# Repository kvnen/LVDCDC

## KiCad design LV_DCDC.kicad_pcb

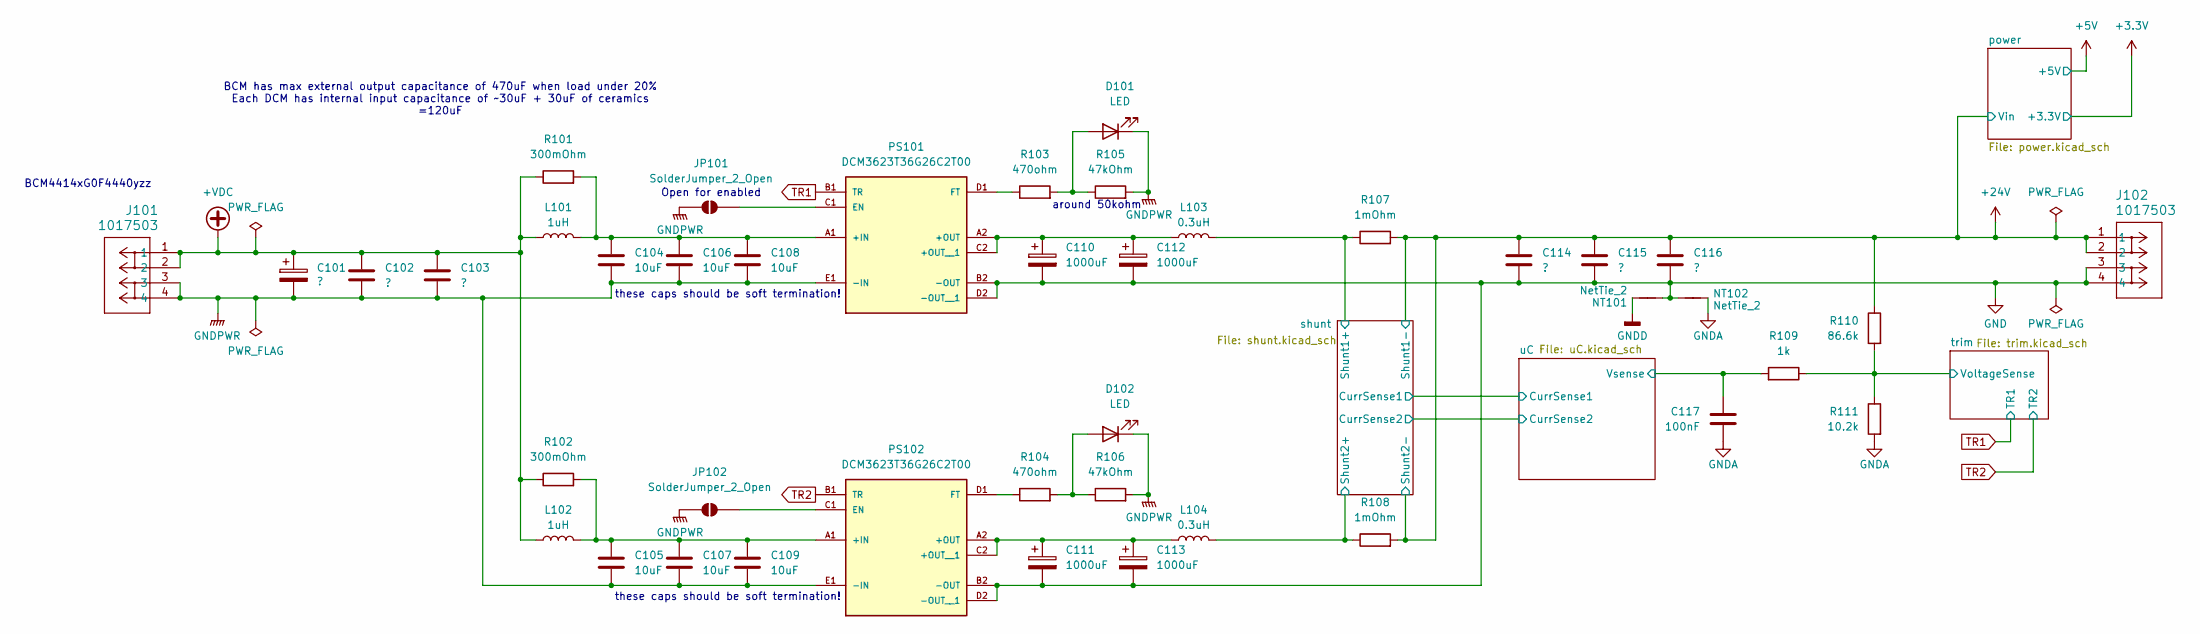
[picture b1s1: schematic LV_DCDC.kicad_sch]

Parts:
C101: ?; CP_Radial_D12.5mm_P5.00mm
C102, C103, C114, C115, C116: ?; C_1206_3216Metric
C104, C105, C106, C107, C108, C109: 10uF; C_1206_3216Metric
C110, C111, C112, C113: 1000uF; CP_Radial_D12.5mm_P5.00mm
C117: 100nF; C_0603_1608Metric
D101, D102: LED; LED_0603_1608Metric
J101, J102: 1017503; CONN_1017491
JP101, JP102: SolderJumper_2_Open; SolderJumper-2_P1.3mm_Open_TrianglePad1.0x1.5mm
L101, L102: 1uH; L_Bourns_SRP1770TA_16.9x16.9mm
L103, L104: 0.3uH; L_APV_APH1040
NT101, NT102: NetTie_2; NetTie-2_SMD_Pad2.0mm
PS101, PS102: DCM3623T36G26C2T00; CONV_DCM3623T36G26C2T00; PARTREV 1.2
R101, R102: 300mOhm; R_1206_3216Metric
R103, R104: 470ohm; R_0603_1608Metric
R105, R106: 47kOhm; R_0603_1608Metric
R107, R108: 1mOhm; R_2512_6332Metric
R109: 1k; R_0603_1608Metric
R110: 86.6k; R_0603_1608Metric
R111: 10.2k; R_0603_1608Metric

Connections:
+24V: C114.1, C115.1, C116.1, J102.1, J102.2, R107.2, R108.2, R110.1; also elsewhere on the board
+VDC: C101.1, C102.1, C103.1, J101.1, J101.2, L101.1, L102.1, R101.1, R102.1
/shunt/Shunt1+: L103.2, R107.1; also elsewhere on the board
/shunt/Shunt2+: L104.2, R108.1; also elsewhere on the board
/trim/VoltageSense: R109.1, R110.2, R111.1; also elsewhere on the board
/uC/Vsense: C117.1, R109.2; also elsewhere on the board
GND: C110.2, C111.2, C112.2, C113.2, C114.2, C115.2, C116.2, J102.3, J102.4, NT101.2, NT102.2, PS101.B2 (-OUT), PS101.D2 (-OUT__1), PS102.B2 (-OUT), PS102.D2 (-OUT__1)
GNDA: C117.2, NT102.1, R111.2; also elsewhere on the board
GNDD: NT101.1; also elsewhere on the board
GNDPWR: C101.2, C102.2, C103.2, C104.2, C105.2, C106.2, C107.2, C108.2, C109.2, D101.1 (K), D102.1 (K), J101.3, J101.4, JP101.2 (B), JP102.2 (B), PS101.E1 (-IN), PS102.E1 (-IN), R105.2, R106.2; also elsewhere on the board
unnamed: D101.2 (A), R103.2, R105.1
unnamed: D102.2 (A), R104.2, R106.1
unnamed: JP101.1 (A), PS101.C1 (EN)
unnamed: JP102.1 (A), PS102.C1 (EN)
unnamed: C104.1, C106.1, C108.1, L101.2, PS101.A1 (+IN), R101.2
unnamed: C110.1, C112.1, L103.1, PS101.A2 (+OUT), PS101.C2 (+OUT__1)
unnamed: PS101.D1 (FT), R103.1
unnamed: C105.1, C107.1, C109.1, L102.2, PS102.A1 (+IN), R102.2
unnamed: C111.1, C113.1, L104.1, PS102.A2 (+OUT), PS102.C2 (+OUT__1)
unnamed: PS102.D1 (FT), R104.1
TR1: PS101.B1 (TR); also elsewhere on the board
TR2: PS102.B1 (TR); also elsewhere on the board

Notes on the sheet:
around 50kohm
Open for enabled
these caps should be soft termination!
BCM has max external output capacitance of 470uF when load under 20% Each DCM has internal input capacitance of ~30uF + 30uF of ceramics =120uF
BCM4414xG0F4440yzz

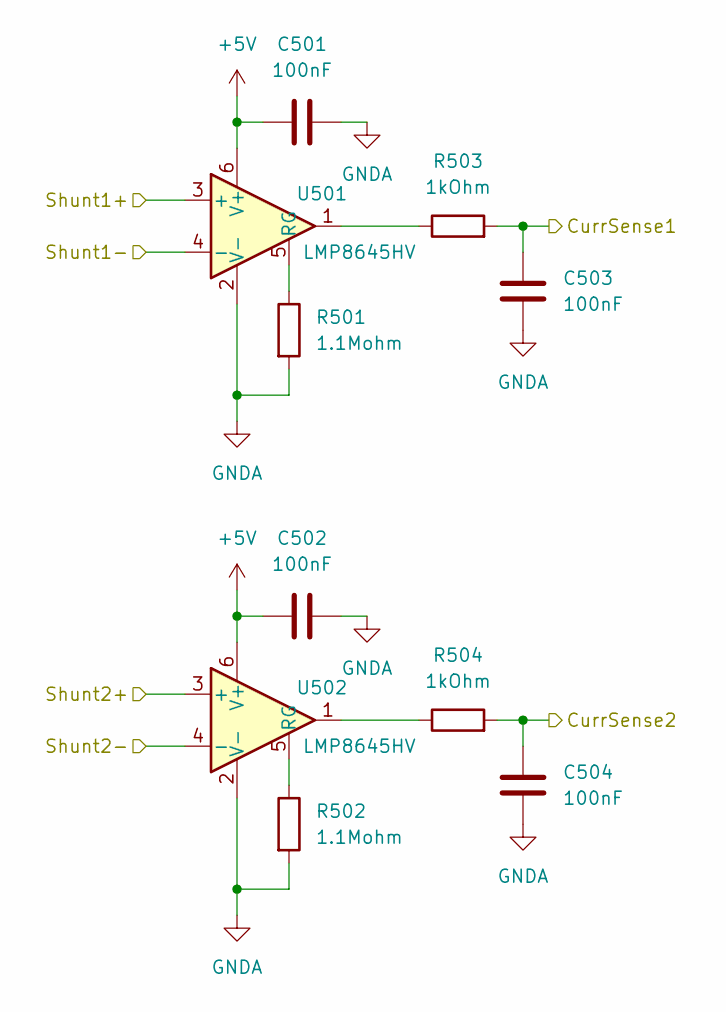
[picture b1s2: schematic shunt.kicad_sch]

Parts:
C501, C502, C503, C504: 100nF; C_0603_1608Metric
R501, R502: 1.1Mohm; R_0603_1608Metric
R503, R504: 1kOhm; R_0603_1608Metric
U501, U502: LMP8645HV; TSOT-23-6_HandSoldering

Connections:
+5V: C501.1, C502.1, U501.6 (V+), U502.6 (V+); also elsewhere on the board
+24V: U501.4 (-), U502.4 (-); also elsewhere on the board
/shunt/CurrSense1: C503.1, R503.2; also elsewhere on the board
/shunt/CurrSense2: C504.1, R504.2; also elsewhere on the board
/shunt/Shunt1+: U501.3 (+); also elsewhere on the board
/shunt/Shunt2+: U502.3 (+); also elsewhere on the board
GNDA: C501.2, C502.2, C503.2, C504.2, R501.2, R502.2, U501.2 (V-), U502.2 (V-); also elsewhere on the board
unnamed: R503.1, U501.1
unnamed: R504.1, U502.1
unnamed: R501.1, U501.5 (RG)
unnamed: R502.1, U502.5 (RG)

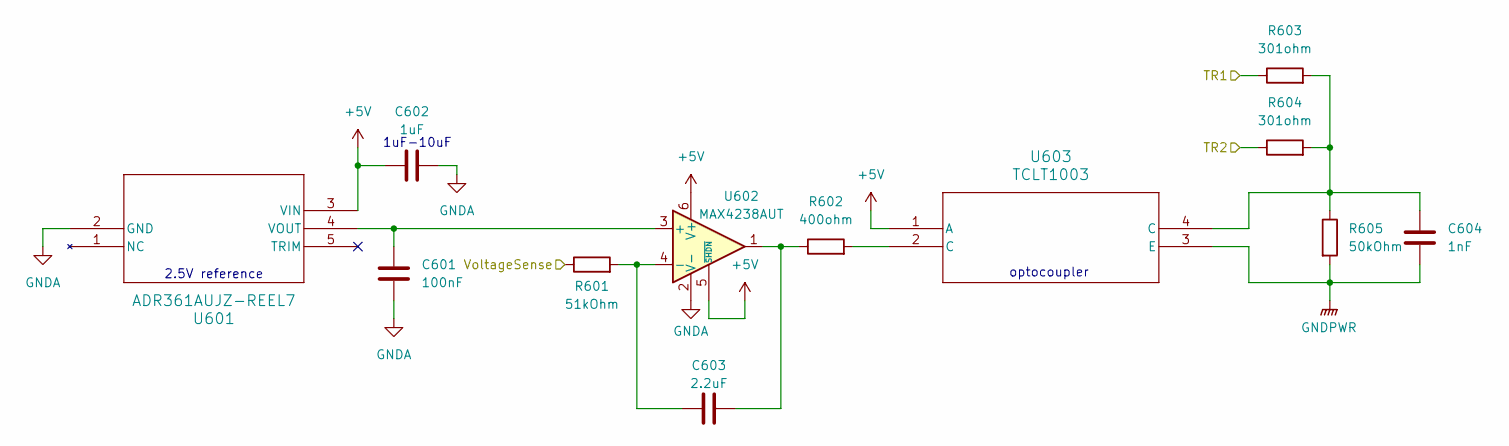
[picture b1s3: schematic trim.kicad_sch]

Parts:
C601: 100nF; C_0603_1608Metric
C602: 1uF; C_0603_1608Metric
C603: 2.2uF; C_0603_1608Metric
C604: 1nF; C_0603_1608Metric
R601: 51kOhm; R_0603_1608Metric
R602: 400ohm; R_0603_1608Metric
R603, R604: 301ohm; R_0603_1608Metric
R605: 50kOhm; R_0603_1608Metric
U601: ADR361AUJZ-REEL7; UJ_5_ADI
U602: MAX4238AUT; SOT-23-6
U603: TCLT1003; SOP-4L_TC

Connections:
+5V: C602.1, U601.3 (VIN), U602.5 (~SHDN), U602.6 (V+), U603.1 (A); also elsewhere on the board
/trim/VoltageSense: R601.1; also elsewhere on the board
GNDA: C601.2, C602.2, U601.2 (GND), U602.2 (V-); also elsewhere on the board
GNDPWR: C604.2, R605.2, U603.3 (E); also elsewhere on the board
unnamed: C603.2, R602.1, U602.1
unnamed: C604.1, R603.2, R604.2, R605.1, U603.4 (C)
unnamed: R602.2, U603.2 (C)
unnamed: C601.1, U601.4 (VOUT), U602.3 (+)
unnamed: C603.1, R601.2, U602.4 (-)
TR1: R603.1; also elsewhere on the board
TR2: R604.1; also elsewhere on the board

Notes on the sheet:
2.5V reference
optocoupler
1uF-10uF

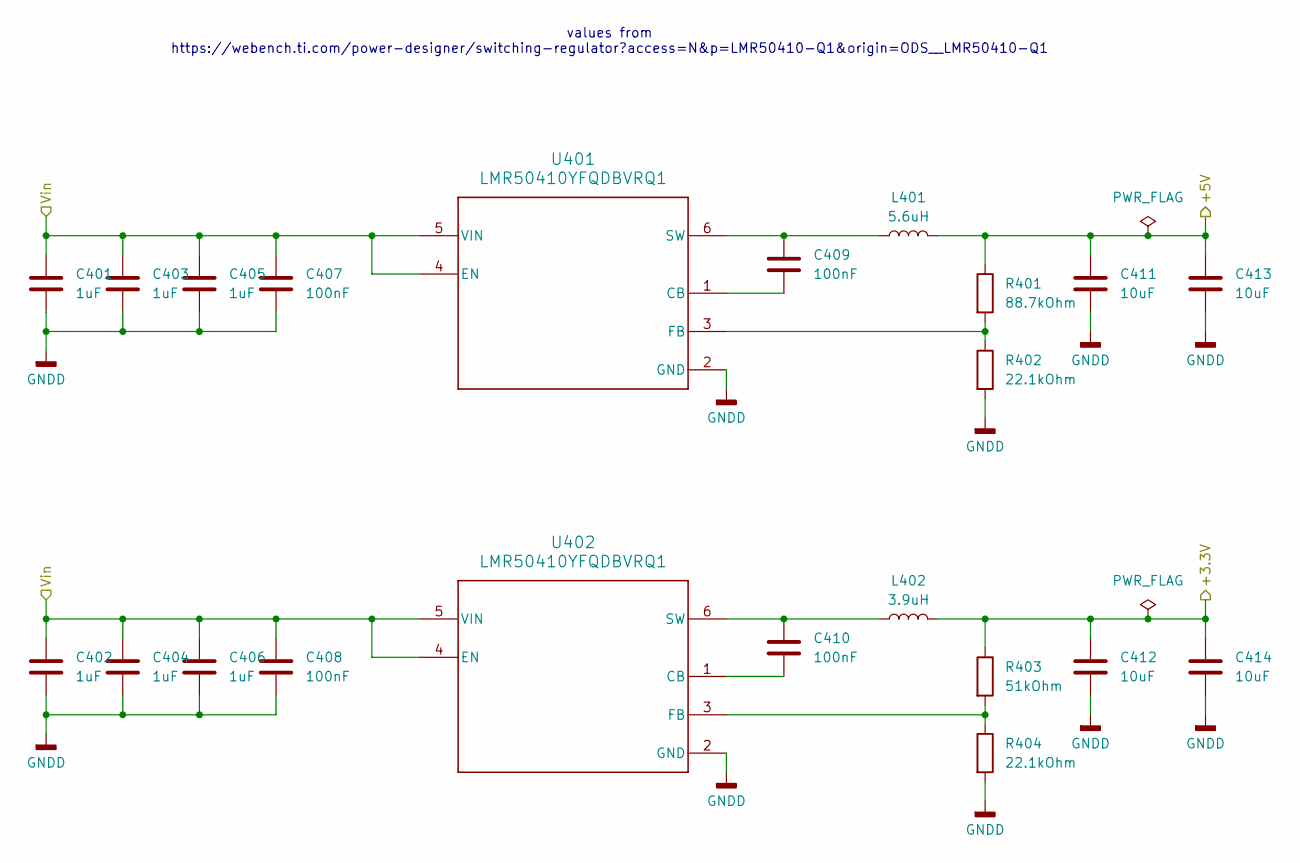
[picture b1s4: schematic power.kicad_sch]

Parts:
C401, C402, C403, C404, C405, C406: 1uF; C_1206_3216Metric
C407, C408, C409, C410: 100nF; C_0603_1608Metric
C411, C412, C413, C414: 10uF; C_1206_3216Metric
L401: 5.6uH; L_1812_4532Metric
L402: 3.9uH; L_1812_4532Metric
R401: 88.7kOhm; R_0603_1608Metric
R402, R404: 22.1kOhm; R_0603_1608Metric
R403: 51kOhm; R_0603_1608Metric
U401, U402: LMR50410YFQDBVRQ1; DBV0006A-IPC_A

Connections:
+3.3V: C412.1, C414.1, L402.2, R403.1; also elsewhere on the board
+5V: C411.1, C413.1, L401.2, R401.1; also elsewhere on the board
+24V: C401.1, C402.1, C403.1, C404.1, C405.1, C406.1, C407.1, C408.1, U401.4 (EN), U401.5 (VIN), U402.4 (EN), U402.5 (VIN); also elsewhere on the board
GNDD: C401.2, C402.2, C403.2, C404.2, C405.2, C406.2, C407.2, C408.2, C411.2, C412.2, C413.2, C414.2, R402.2, R404.2, U401.2 (GND), U402.2 (GND); also elsewhere on the board
unnamed: C409.2, U401.1 (CB)
unnamed: R401.2, R402.1, U401.3 (FB)
unnamed: C409.1, L401.1, U401.6 (SW)
unnamed: C410.2, U402.1 (CB)
unnamed: R403.2, R404.1, U402.3 (FB)
unnamed: C410.1, L402.1, U402.6 (SW)

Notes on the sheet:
values from https://webench.ti.com/power-designer/switching-regulator?access=N&p=LMR50410-Q1&origin=ODS__LMR50410-Q1

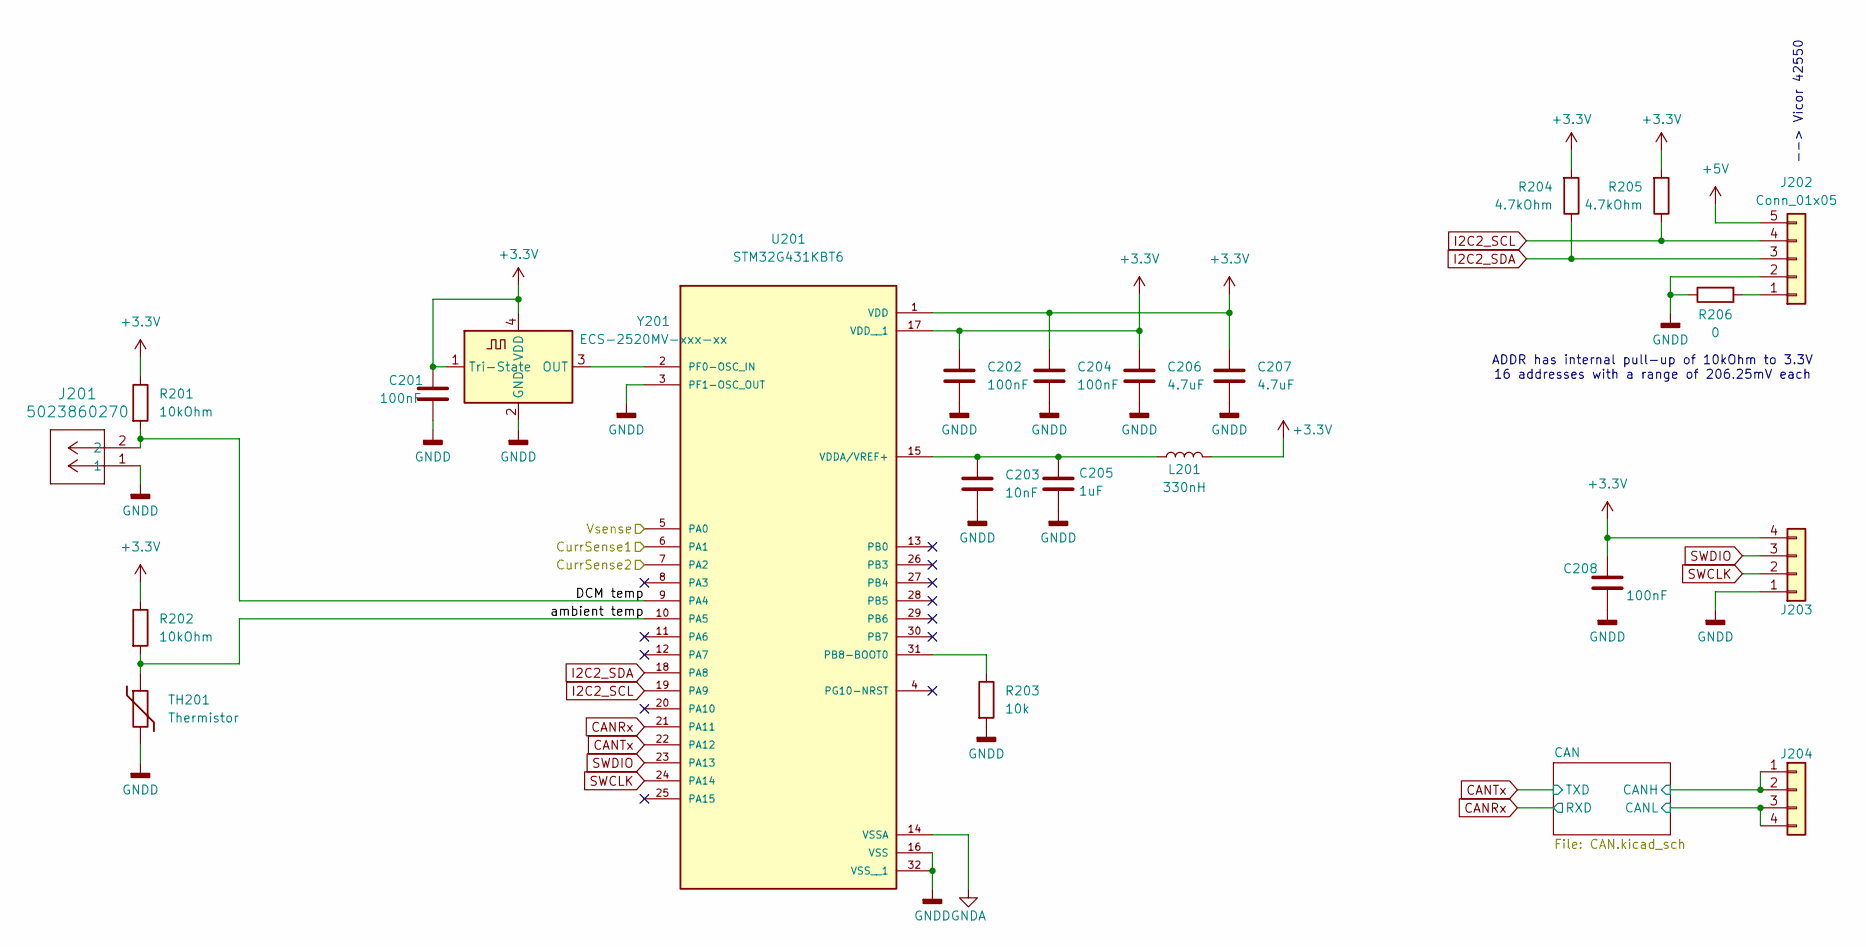
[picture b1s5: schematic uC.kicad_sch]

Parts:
C201, C202, C204: 100nF; C_0603_1608Metric
C203: 10nF; C_0603_1608Metric
C205: 1uF; C_0603_1608Metric
C206, C207: 4.7uF; C_0603_1608Metric
C208: 100nF; C_0805_2012Metric_Pad1.18x1.45mm_HandSolder; TOLERANCE (FILL IN AS +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 10%
J201: 5023860270; CONN_502386-02xx_MOL
J202: Conn_01x05; PinHeader_2x05_P2.54mm_Vertical
J203: Conn_01x04; PinSocket_1x04_P2.54mm_Vertical
J204: Conn_01x04; PinHeader_2x04_P2.54mm_Vertical
L201: 330nH; L_0805_2012Metric
R201, R202: 10kOhm; R_0603_1608Metric
R203: 10k; R_0603_1608Metric
R204, R205: 4.7kOhm; R_0603_1608Metric
R206: 0; R_0603_1608Metric
TH201: Thermistor; R_0805_2012Metric
U201: STM32G431KBT6; LQFP-32_7x7mm_P0.8mm; PARTREV 2
Y201: ECS-2520MV-xxx-xx; Oscillator_SMD_ECS_2520MV-xxx-xx-4Pin_2.5x2.0mm

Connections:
+3.3V: C201.1, C202.1, C204.1, C206.1, C207.1, C208.1, J203.4, L201.2, R201.1, R202.1, R204.2, R205.2, U201.1 (VDD), U201.17 (VDD__1), Y201.1 (Tri-State), Y201.4 (VDD); also elsewhere on the board
+5V: J202.5; also elsewhere on the board
/shunt/CurrSense1: U201.6 (PA1); also elsewhere on the board
/shunt/CurrSense2: U201.7 (PA2); also elsewhere on the board
/uC/CAN/CANH: J204.1, J204.2; also elsewhere on the board
/uC/CAN/CANL: J204.3, J204.4; also elsewhere on the board
/uC/DCM temp: J201.2, R201.2, U201.9 (PA4)
/uC/Vsense: U201.5 (PA0); also elsewhere on the board
/uC/ambient temp: R202.2, TH201.1, U201.10 (PA5)
CANRx: U201.21 (PA11); also elsewhere on the board
CANTx: U201.22 (PA12); also elsewhere on the board
GNDA: U201.14 (VSSA); also elsewhere on the board
GNDD: C201.2, C202.2, C203.2, C204.2, C205.2, C206.2, C207.2, C208.2, J201.1, J202.2, J203.1, R203.2, R206.1, TH201.2, U201.3 (PF1-OSC_OUT), U201.16 (VSS), U201.32 (VSS__1), Y201.2 (GND); also elsewhere on the board
I2C2_SCL: J202.4, R205.1, U201.19 (PA9)
I2C2_SDA: J202.3, R204.1, U201.18 (PA8)
unnamed: J202.1, R206.2
unnamed: R203.1, U201.31 (PB8-BOOT0)
unnamed: U201.2 (PF0-OSC_IN), Y201.3 (OUT)
unnamed: C203.1, C205.1, L201.1, U201.15 (VDDA/VREF+)
SWCLK: J203.2, U201.24 (PA14)
SWDIO: J203.3, U201.23 (PA13)

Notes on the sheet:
--> Vicor 42550
ADDR has internal pull-up of 10kOhm to 3.3V 16 addresses with a range of 206.25mV each

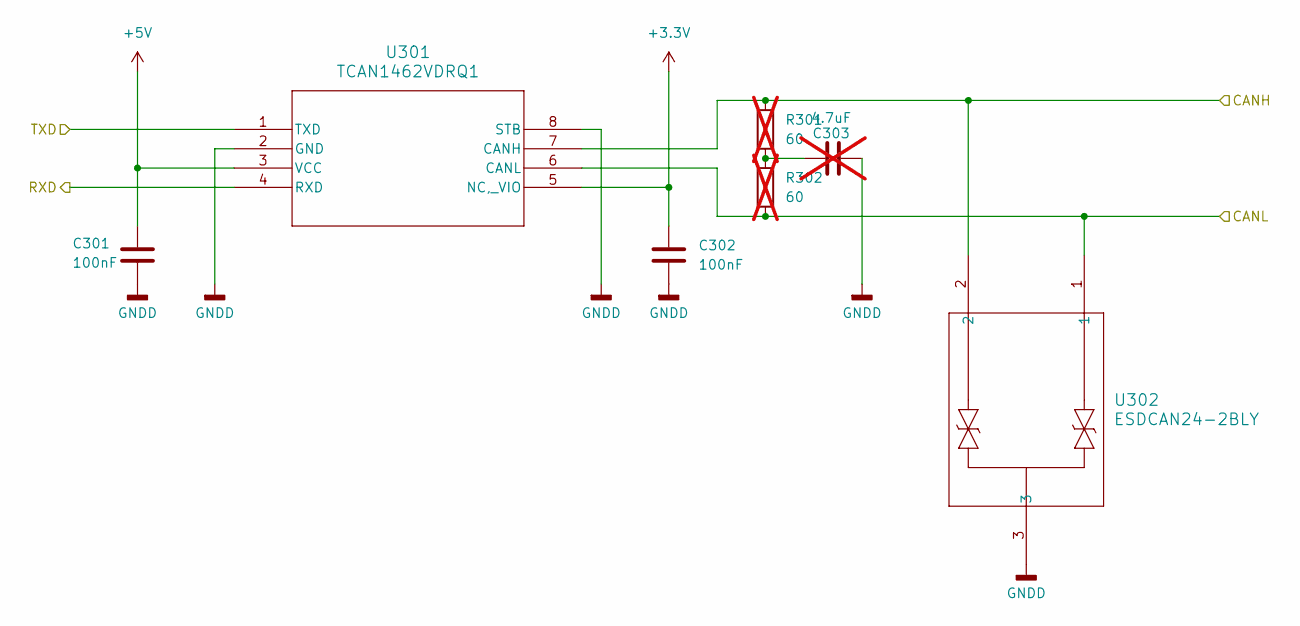
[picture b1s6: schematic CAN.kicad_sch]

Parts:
C301, C302: 100nF; C_0603_1608Metric
C303: 4.7uF; C_0603_1608Metric; not fitted
R301, R302: 60; R_0603_1608Metric; not fitted
U301: TCAN1462VDRQ1; SOIC8_D_TEX
U302: ESDCAN24-2BLY; SOT_24-2BLY_STM

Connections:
+3.3V: C302.1, U301.5 (NC,_VIO); also elsewhere on the board
+5V: C301.1, U301.3 (VCC); also elsewhere on the board
/uC/CAN/CANH: R301.1, U301.7 (CANH), U302.2; also elsewhere on the board
/uC/CAN/CANL: R302.2, U301.6 (CANL), U302.1; also elsewhere on the board
CANRx: U301.4 (RXD); also elsewhere on the board
CANTx: U301.1 (TXD); also elsewhere on the board
GNDD: C301.2, C302.2, C303.1, U301.2 (GND), U301.8 (STB), U302.3; also elsewhere on the board
unnamed: C303.2, R301.2, R302.1

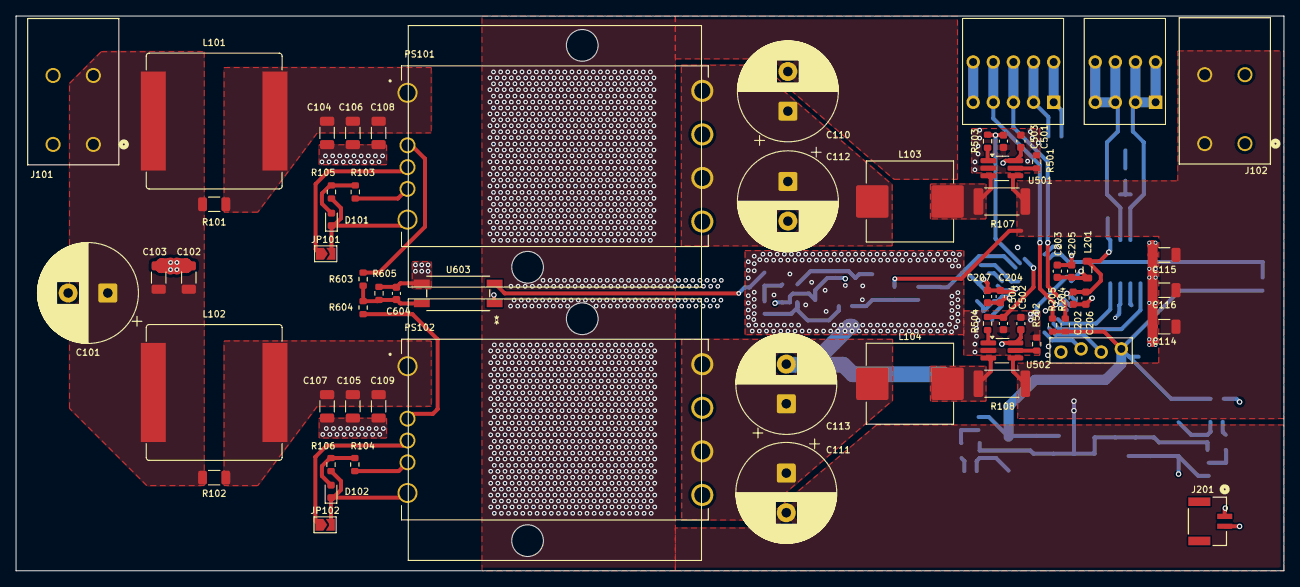
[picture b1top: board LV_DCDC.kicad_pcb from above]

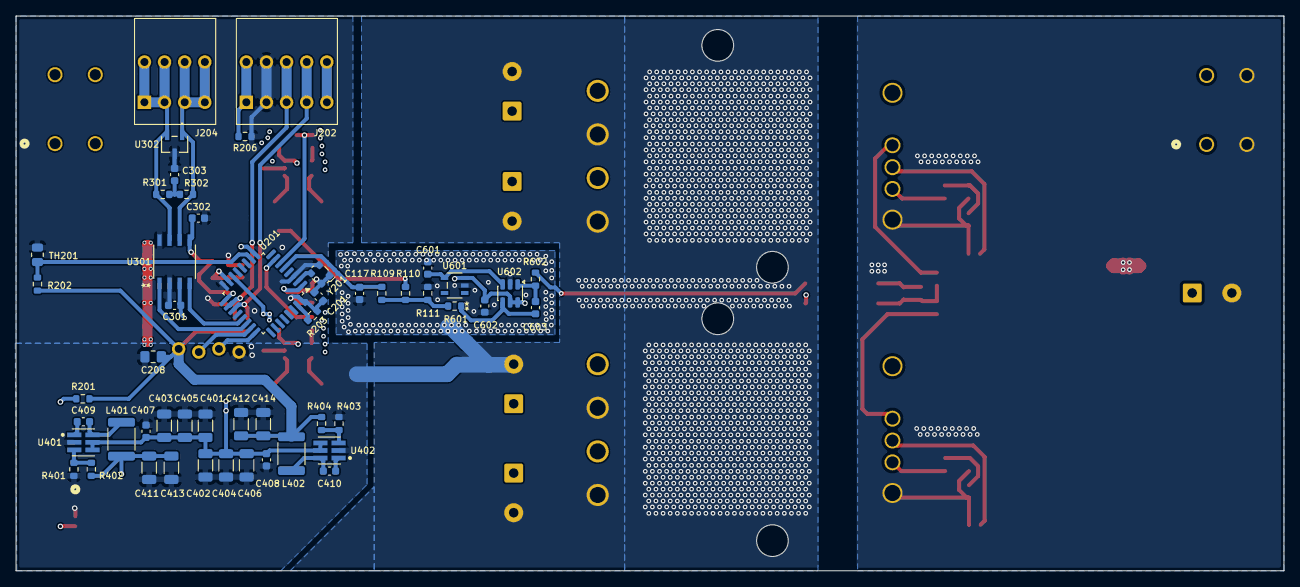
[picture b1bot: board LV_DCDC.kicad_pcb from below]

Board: 4 copper layers, 160.0 x 70.0 mm, 115 parts (53 on the bottom side), 56 nets.

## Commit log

2026-03-24 uC schema added
2026-03-24 added stuff to library
2026-03-24 added xtal
2026-03-29 found the correct i2c logic level shifter.
2026-03-29 made todo, added power
2026-03-30 fixed bcm connector, added thermistors something else too prolly
2026-03-30 moved to kicad 10
2026-03-31 did some stuff yesterday i dont remember
2026-04-19 started on shunt
2026-04-20 Made trim circuit
2026-04-21 added shunts
2026-04-21 assigned footprints, some minor schematic stuff, started layout
2026-04-22 progress on layout in general, minor tweaks to schemas
2026-04-22 made heatsink holes
2026-04-25 Layout done except for silkscreen
2026-04-26 moved the accuracy trim to bottom side. added stitching to bottom of DCMs
2026-04-28 fixed ref. des. on silk screen
2026-04-30 added heatsink mounting holes
2026-04-30 heat sink mount holes
